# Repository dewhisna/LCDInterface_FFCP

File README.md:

# LCDInterface_FFCP

This repository contains custom LCD/SDCard/Keypad Interface board designs for the FlashForge Creator Pro printer (primarily the 2016 model FFCP).

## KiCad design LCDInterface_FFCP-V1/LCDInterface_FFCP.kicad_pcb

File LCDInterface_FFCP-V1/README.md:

# FlashForge 2016 LCD/SDCard/Keypad Interface

See this on Thingiverse: [https://www.thingiverse.com/thing:2007070](https://www.thingiverse.com/thing:2007070).

I'm tired of having SDCard read issues on my FlashForge Creator Pro 2016 printers.  I have three of those printers and all three have issues.  After digging through and analyzing the schematics, I think the primary culprit is either ringing or a slight timing skew between the SCLK timebase and the unbuffered MISO data output from the SDCard.  SDCards aren't designed to drive their data output down a 300mm ribbon cable.

Then if you add the other issues of no bypass capacitors, limited decoupling capacitors, no ESD protection, long off-board 3.3V power runs, and abuse of a 74AHC125 as a voltage level translator, it's a wonder, as Gary described with his [LCD ESD Protection board](https://www.thingiverse.com/thing:91656), "that it works at all".

I originally looked at just building one of [Gary's LCD ESD Protection boards](https://www.thingiverse.com/thing:91656) for each of my printers, since the circuit in my FlashForge Creator Pro 2016 printers is nearly identical to the Replicator design.  But, I decided that it physically wouldn't fit the printer all that well.

Since I had to make the boards regardless, I decided instead to completely redesign the main LCD Interface Board of the FlashForge -- which is the bottom board in the stack inside the LCD panel where the LCD and Keypad boards plug into.  That board had plenty of free space on it that could be used for the additional circuitry.  So, I took the circuit of the FlashForge Interface, which wasn't difficult to sketch out since it's nearly identical to the MakerBot Replicator Interface, and added the components of [Gary's LCD ESD Protection board](https://www.thingiverse.com/thing:91656) to it.

This board is the result...  a new drop-in replacement for the original FlashForge LCD Interface.  The only extra connection is the ESD Ground connection pad, which is designed to have a wire soldered to it and run to the chassis ground of the printer, which has a nice, convenient terminal connector in the electronics compartment of the printer near the power supply (see the posted pictures).  Unlike Gary's situation, the FFCP has some metal chassis parts already and has an earth ground in place, which is really convenient.

This board also adds pads for both the red and green LEDs that have signal runs from the MightyBoard, which are completely omitted on the original FlashForge Interface.  They may be useful if you are doing custom firmware coding work and need some extra LEDs for debugging and feedback -- otherwise, just don't populate them when you build this board.

I also added an option for an adjustable contrast control for the LCD, in addition to pads for the fixed resistor values that the FlashForge Interface uses.  This allows you to populate it either way.  If you want the simple, fixed-level contrast like the FFCP has, just populate the two fixed resistors that set that.  If you want to control it manually, mount the potentiometer instead.  Just don't mount both sets of components on the board or else the contrast level control will be a little wonky.

The board is nearly all surface-mount parts, but I used the larger 1206 size parts for the discrete components and I used the larger copper landing zones on all the footprints on the PCB to make it easier to hand-solder, though while assembling mine, I found the larger pads on the 1206 parts a bit annoying.

The hardest pieces to solder are the 74LVC1T45 chips, being a TSSOP-6 package with 0.65mm lead spacing.  TSSOPs are easier to hand-solder than you might think, but you will need a decent soldering iron, a bright work light, a magnifier glass, and some solder wick.  When assembling these boards, start with those pieces first so that the other components aren't in your way.  Also, after doing the TSSOP's, the SOIC's will feel huge and so will the rest of the components. 

Boards can be ordered from OSHPark: [https://www.oshpark.com/shared_projects/4YWmcdYh](https://www.oshpark.com/shared_projects/4YWmcdYh)

The schematic, bill-of-materials, and PCB Gerber files have been posted here in the files section.

**Update (15-Jan-2017)**: I've received my boards from OSHPark and got them assembled.  It came up and ran fine first time with no issues.  So I've removed the "work in progress" flag.

I did make one last-minute change in the parts I used from what is posted in the bill-of-materials.  I decided to use a 0.001uF (1000pF) capacitor for C2 for the loading on the SDCard SCLK signal, instead of the 0.1uF.  I decided on this change after running some numbers on the signal rise-time change that the added capacitor will create for the frequencies I believe the ATmega would most likely be using for the SDCard, based largely on calculation details in the textbook "High-Speed Digital Design: A Handbook of Black Magic".  As far as I know, either value will work.  The 0.001uF is working fine on my boards, and Gary previously proved out the 0.1uF on the board in his design.  I just felt more comfortable with the 0.001uF part.  So the part I actually used for C2 was DigiKey 709-1036-1-ND.

Otherwise, my boards were assembled as-per the diagram and bill-of-materials.  And I did install the ferrite cable clamp that Gary suggested, as seen in my posted pictures and included in the bill-of-materials.

So far the new board has been working with no issues and with no read errors from the SDCard.  Though the original FlashForge board worked OK sometimes too, so only time will confirm if I have truly solved the SDCard issues I previously had.

If I were to make any changes to the board on a future version, I would reduce the size of the 1206 SMD pads a bit, as I found them a bit annoying during hand-soldering with them being so large, even though the larger pads supposedly facilitates hand-soldering.  And, I would increase the annular ring size of the vias.  The vias seem to be fine and are working well, but I always feel more comfortable being generous with design rules, and they came out a bit smaller than I had intended.  And I would move the LEDs and the contrast control to the other side of the board to where they can be used with the LCD installed, making it possible to drill holes in the plastic LCD panel to access them.

For reference, I posted a picture of my board along side the original (green) FlashForge board so you can compare them.

**Update (23-Jan-2018)**: It's now been a full year since I built these to go on my FlashForge printers.  And I'm happy to report that with these boards, I've had zero read failures from the SDCard on any of my three printers, and they've logged many hundreds of hours of printing.  On the original boards that came with the printer, I experienced a read failure roughly six times out of every ten card insertions.  I believe I can safely claim they have completely resolved my SDCard issues.

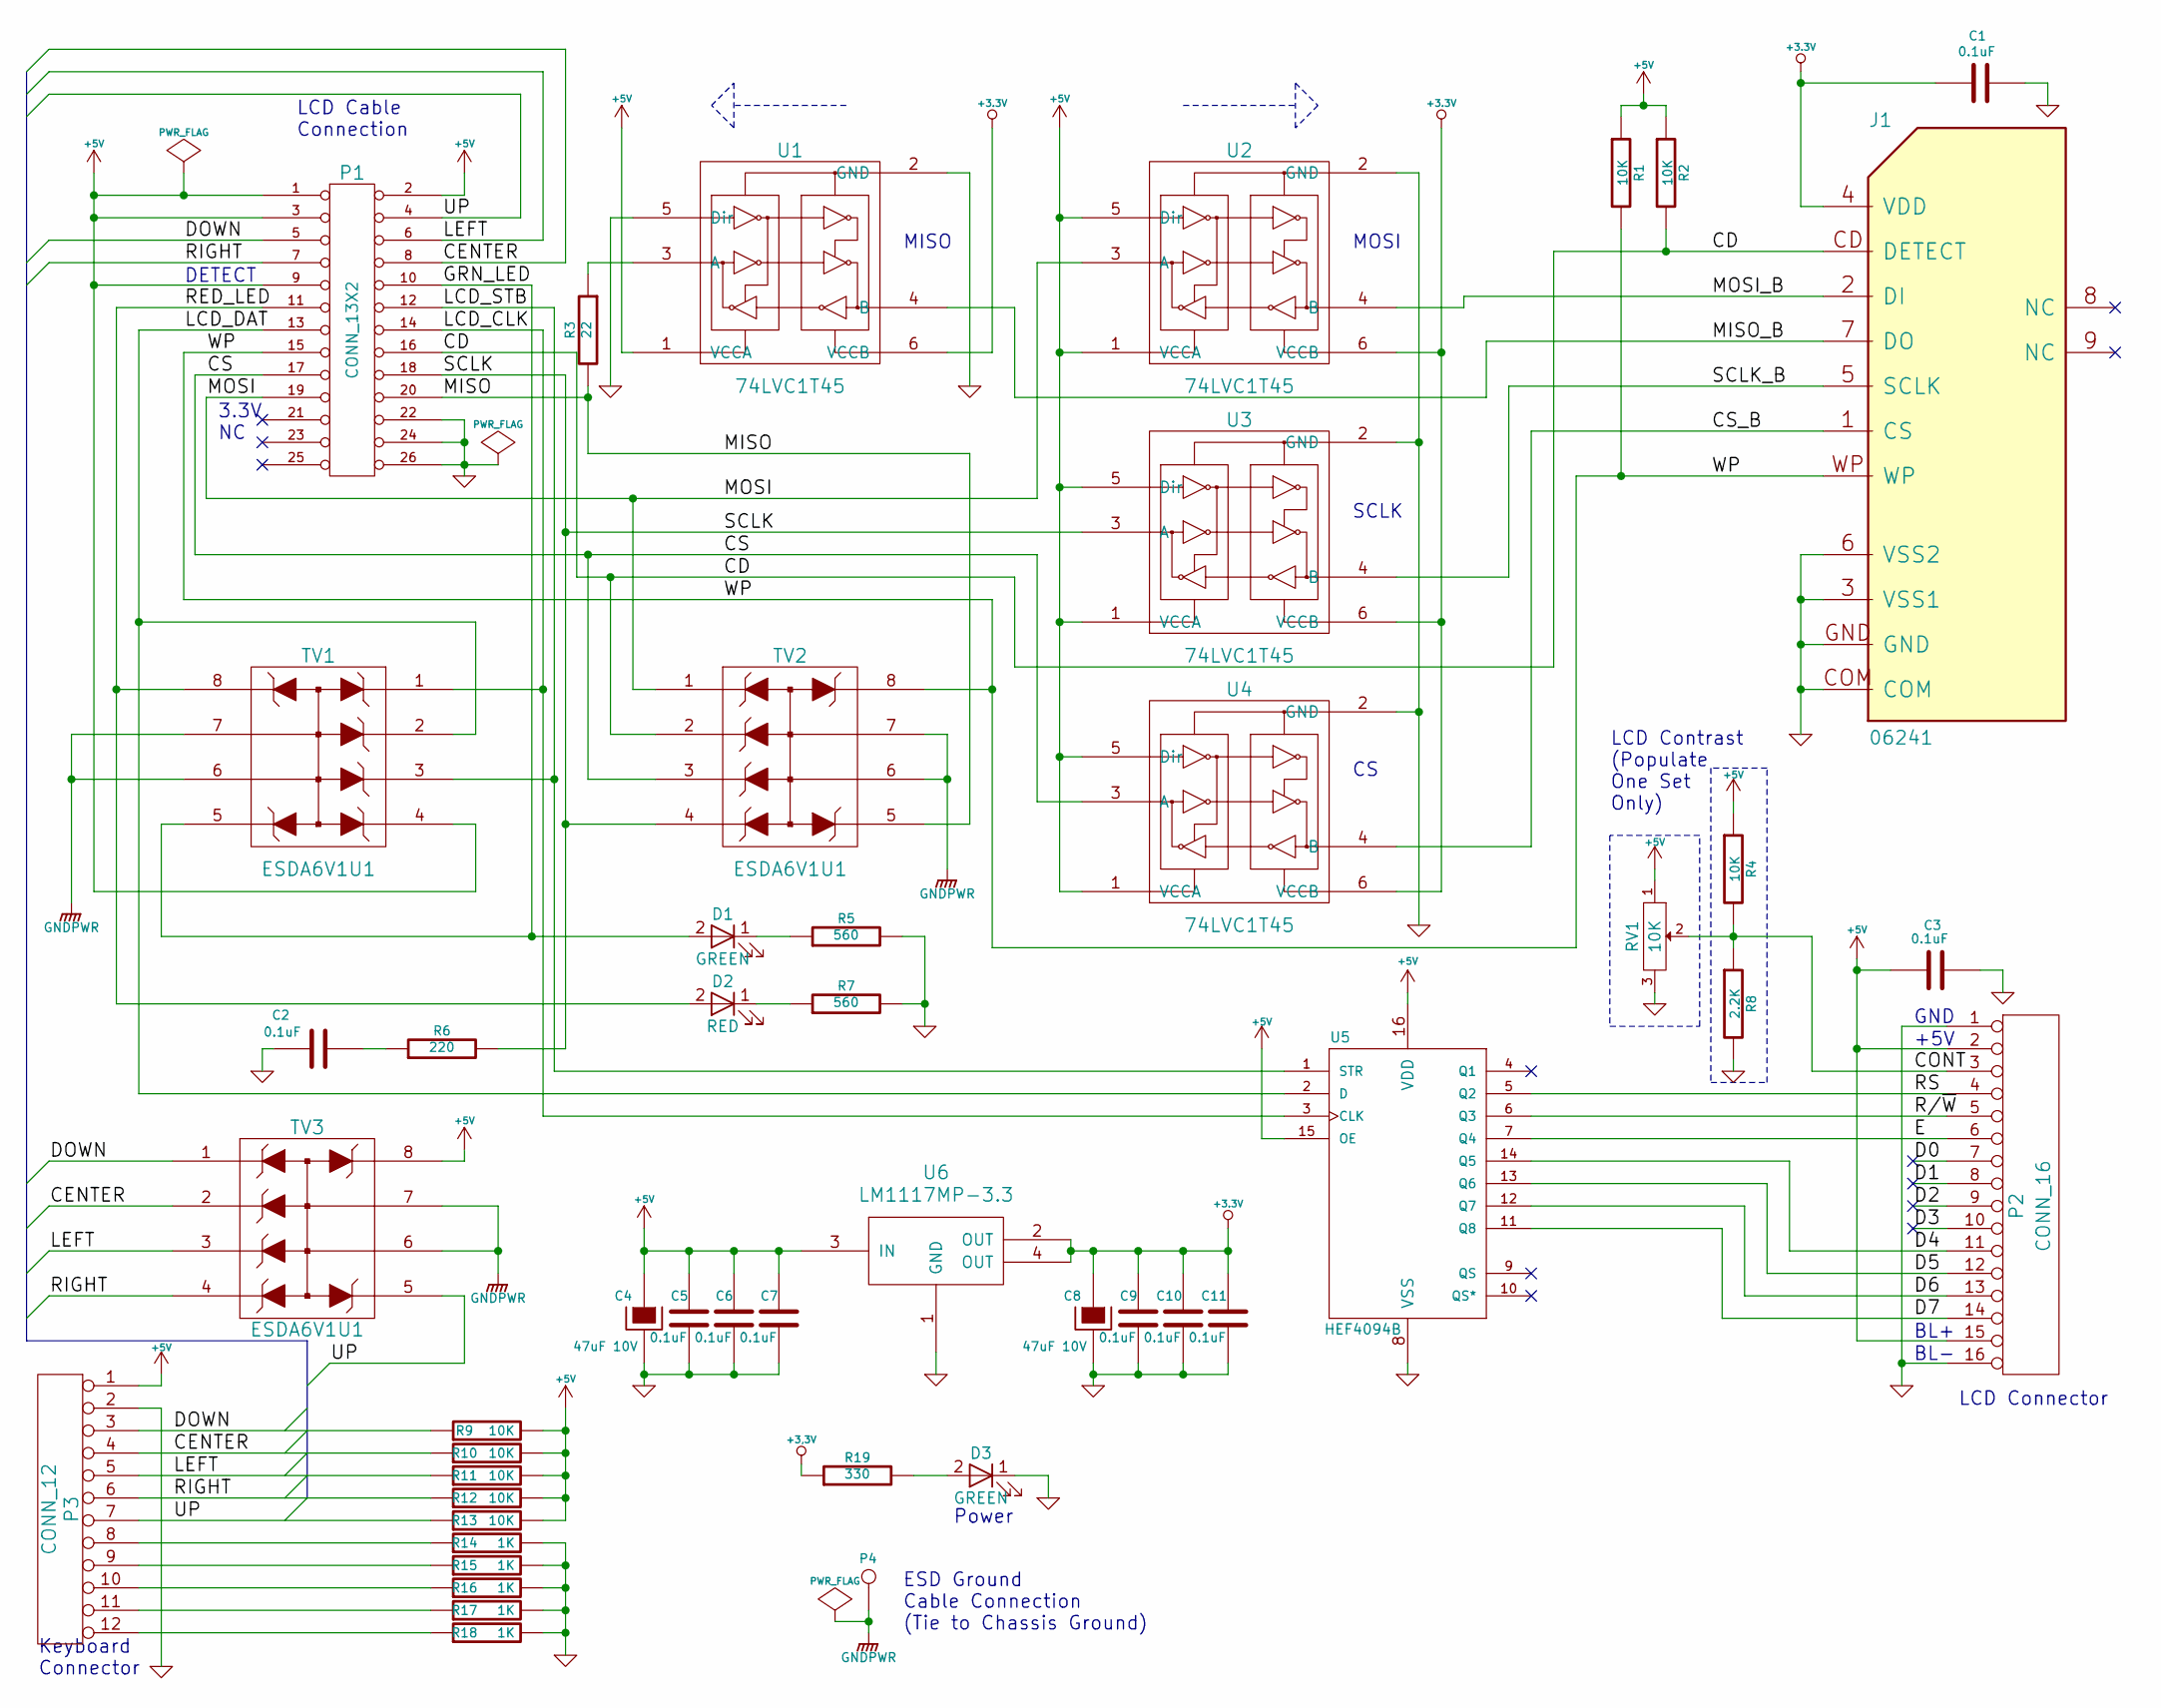
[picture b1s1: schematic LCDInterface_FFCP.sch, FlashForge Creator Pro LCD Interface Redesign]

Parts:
C1, C2, C3, C5, C6, C7, C9, C10, C11: 0.1uF; C_1206_HandSoldering
C4, C8: 47uF 10V; c_elec_6.3x5.8
D1, D3: GREEN; LED_1206
D2: RED; LED_1206
J1: 06241; SDCARD-SOCKET
P1: CONN_13X2; PAK100_2500-5-26
P2: CONN_16; con-molex-70543-16
P3: CONN_12; con-molex-70543-12
P4: CONN_1; 1pin
R1, R2, R4, R9, R10, R11, R12, R13: 10K; R_1206_HandSoldering
R3: 22; R_1206_HandSoldering
R5, R7: 560; R_1206_HandSoldering
R6: 220; R_1206_HandSoldering
R8: 2.2K; R_1206_HandSoldering
R14, R15, R16, R17, R18: 1K; R_1206_HandSoldering
R19: 330; R_1206_HandSoldering
RV1: 10K; Potentiometer_Trimmer-EVM3E
TV1, TV2, TV3: ESDA6V1U1; 74xx-us-SO08
U1, U2, U3, U4: 74LVC1T45; SC-70-6_Handsoldering
U5: HEF4094B; 74xx-us-SO16
U6: LM1117MP-3.3; SOT-223

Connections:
+5V: C3.1, C4.1, C5.1, C6.1, C7.1, P1.1, P1.2, P1.3, P1.9, P2.2, P2.15, P3.1, R1.1, R2.1, R4.1, R9.2, R10.2, R11.2, R12.2, R13.2, RV1.1, TV1.4 (I/O_4), TV3.8 (I/O_6), U1.1 (VCCA), U2.1 (VCCA), U2.5 (Dir), U3.1 (VCCA), U3.5 (Dir), U4.1 (VCCA), U4.5 (Dir), U5.15 (OE), U5.16 (VDD), U6.3 (IN)
/CD: J1.CD (DETECT), P1.16, R2.2, TV2.2 (I/O_2)
/CENTER: P1.8, P3.4, R10.1, TV3.2 (I/O_2)
/CONT: P2.3, R4.2, R8.1, RV1.2
/CS: P1.17, TV2.3 (I/O_3), U4.3 (A)
/CS_B: J1.1 (CS), U4.4 (B)
/D0: P2.7
/D1: P2.8
/D2: P2.9
/D3: P2.10
/D4: P2.11, U5.14 (Q5)
/D5: P2.12, U5.13 (Q6)
/D6: P2.13, U5.12 (Q7)
/D7: P2.14, U5.11 (Q8)
/DOWN: P1.5, P3.3, R9.1, TV3.1 (I/O_1)
/E: P2.6, U5.7 (Q4)
/GRN_LED: D1.2 (A), P1.10, TV1.5 (I/O_5)
/LCD_CLK: P1.14, TV1.1 (I/O_1), U5.3 (CLK)
/LCD_DAT: P1.13, TV1.2 (I/O_2), U5.2 (D)
/LCD_STB: P1.12, TV1.3 (I/O_3), U5.1 (STR)
/LEFT: P1.6, P3.5, R11.1, TV3.3 (I/O_3)
/MISO: P1.20, R3.2, TV2.5 (I/O_5)
/MISO_B: J1.7 (DO), U1.4 (B)
/MOSI: P1.19, TV2.1 (I/O_1), U2.3 (A)
/MOSI_B: J1.2 (DI), U2.4 (B)
/R/~W: P2.5, U5.6 (Q3)
/RED_LED: D2.2 (A), P1.11, TV1.8 (I/O_6)
/RIGHT: P1.7, P3.6, R12.1, TV3.4 (I/O_4)
/RS: P2.4, U5.5 (Q2)
/SCLK: P1.18, R6.2, TV2.4 (I/O_4), U3.3 (A)
/SCLK_B: J1.5 (SCLK), U3.4 (B)
/UP: P1.4, P3.7, R13.1, TV3.5 (I/O_5)
/WP: J1.WP, P1.15, R1.2, TV2.8 (I/O_6)
GNDPWR: P4.1, TV1.6 (GND), TV1.7 (GND), TV2.6 (GND), TV2.7 (GND), TV3.6 (GND), TV3.7 (GND)
unnamed: C2.2, R6.1
unnamed: D1.1 (K), R5.1
unnamed: D2.1 (K), R7.1
unnamed: D3.2 (A), R19.2
unnamed: P3.8, R14.1
unnamed: P3.9, R15.1
unnamed: P3.10, R16.1
unnamed: P3.11, R17.1
unnamed: P3.12, R18.1
unnamed: R3.1, U1.3 (A)

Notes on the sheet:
GND
+5V
LCD Contrast (Populate One Set Only)
BL+
BL-
LCD Cable Connection
LCD Connector
Keyboard Connector
3.3V NC
MOSI
SCLK
MISO
DETECT
Power
ESD Ground Cable Connection (Tie to Chassis Ground)

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
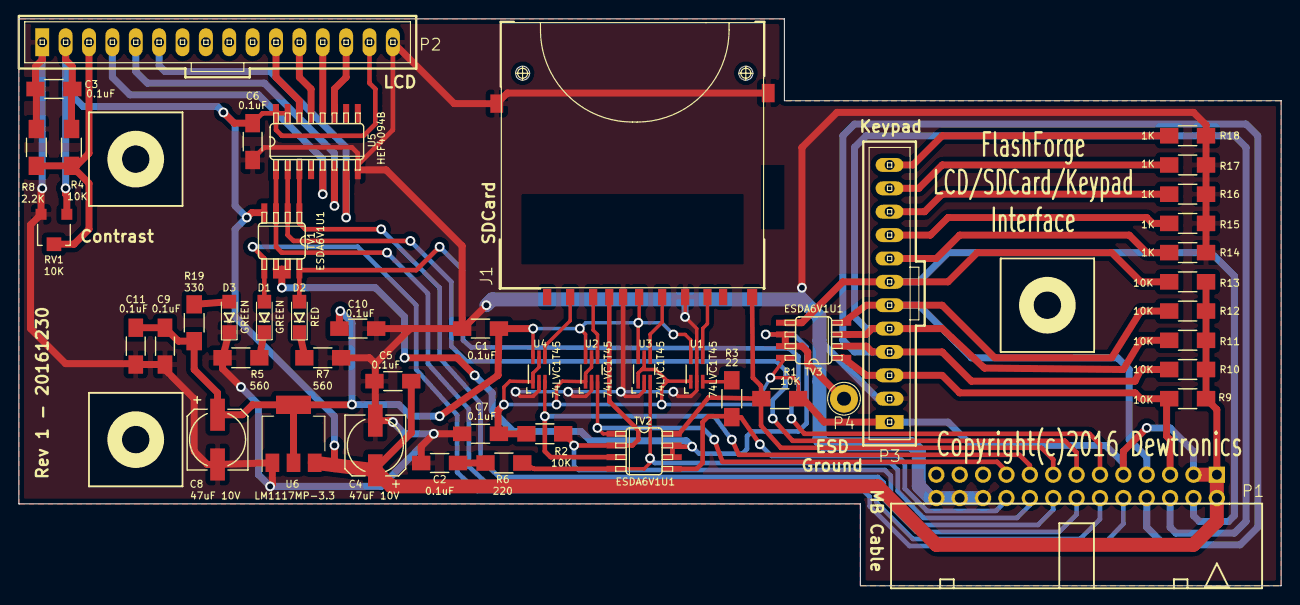
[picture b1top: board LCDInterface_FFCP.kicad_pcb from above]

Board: 2 copper layers, 137.2 x 61.6 mm, 51 parts (0 on the bottom side), 42 nets.

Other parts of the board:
1PIN, 1PIN#2, 1PIN#3: P***; 1pin

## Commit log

2019-07-04 Extract LCDInterface_FFCP out of large private repo to separate public repo.

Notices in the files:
LCDInterface_FFCP-V1/LCDInterface_FFCP.kicad_pcb:
Copyright(c)2016 Dewtronics
